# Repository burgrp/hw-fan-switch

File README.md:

# hw-fan-switch

A small, wirelessly-controlled 12 V DC fan switch. It drives a fan with a
variable PWM duty cycle and is controlled over a BLE long-range radio link,
making it part of the [Bleriot](https://github.com/burgrp/bleriot) node network.

The board is built around a **Puya PY32F003** Cortex-M0+ microcontroller with a
**PAN211x** radio, and the firmware is written in Go and compiled with
[TinyGo](https://tinygo.org/).

## Features

- Variable-speed fan control via hardware PWM (TIM14_CH1 on `PB1`).
- 50 kHz PWM carrier, above the audible range to avoid switching noise.
- Configurable low-speed handling:
  - **Low-duty threshold** — below this duty the fan is treated as stopped and
    the output is forced to 0.
  - **Low-duty kickstart** — a brief higher-duty pulse to overcome fan stiction
    when starting at low speed.
- Wireless control and telemetry over the PAN211x BLE long-range link.
- Yellow status LED is steadily on while the hub is online and flashes briefly
  once per second while offline.
- Device identity, radio settings, and configuration are owned by the site
  inventory and baked into each firmware image at build time.

## Repository layout

| Path | Description |
| --- | --- |
| `board/` | KiCad hardware design (schematic, PCB, BOM, production files). |
| `fw/` | Importable TinyGo firmware and board-owned build profile. |
| `fw/spec/` | Device specification: registers and runtime `Config`. |
| `fw/cmd/dev/` | Optional local development inventory. |
| `sub/hw-kicad/` | Shared KiCad symbol/footprint library (git submodule). |

## Hardware

| Function | Pin |
| --- | --- |
| Yellow status LED | `PB0` |
| Fan PWM output (TIM14_CH1, AF0) | `PB1` |
| Radio SPI clock | `PA2` |
| Radio SPI data | `PA1` |
| Radio SPI chip select | `PA4` |

The status LED is active high. A successfully decoded hub packet keeps the node
online for five seconds. While online the LED remains on; after the timeout it
follows BleRiot's 200 ms on, 800 ms off heartbeat until another packet arrives.

The KiCad project lives in `board/`, with fabrication outputs (Gerbers, BOM,
positions) under `board/production/`.

## Firmware

The firmware is the importable `fanswitch` package. Its TinyGo implementation
exports `Run`, while `fw/spec` exposes `Config`, the register table, chip, and a
typed build/flash profile. BleRiot generates a private external `package main`
inside the deployment module and calls `Run` with that instance's baked identity
and configuration. Nothing is generated in this repository for a deployment
build.

### Prerequisites

- [TinyGo](https://tinygo.org/getting-started/install/)
- [pyOCD](https://pyocd.io/) for flashing and RTT logging
- `arm-none-eabi-objdump` (optional, for disassembly)

Clone with submodules:

```sh
git clone --recurse-submodules https://github.com/burgrp/hw-fan-switch.git
```

### Build and flash

Build deployment firmware from the authoritative site inventory. For the AGC
checkout and its `basement.fan` instance:

```sh
cd /home/paul/git/agc/bleriot

# Inspect the generated entry point without writing it
go run . node gen --name basement.fan

# One-time: install the target CMSIS pack
go run . node install-pack --name basement.fan

# Generate the private entry point and build image.elf
go run . node build --name basement.fan

# Generate, build, flash, and open RTT
go run . node build --name basement.fan --flash --rtt

# Open RTT without flashing
go run . node rtt --name basement.fan
```

The `bleriot node` commands resolve the selected inventory instance. `node
build` generates its identity and `Config` under that deployment's private
`.bleriot` directory, then builds this module using the profile carried by
`spec.Type`. The deployment pins the firmware version in `go.mod`; it does not
carry fan-specific build flags. This repository's Makefile contains optional
aliases for `fw/cmd/dev`.

## Configuration

The inventory `Config` (see `fw/spec/spec.go`) controls runtime behaviour:

| Field | Meaning |
| --- | --- |
| `DefaultDuty` | Fan duty cycle (0–100) applied at startup. |
| `LowDutyThreshold` | Duty below which the fan is forced to 0. `0` disables the threshold. |
| `LowDutyKickstart` | Duty briefly applied to spin up the fan from low speed. `0` disables the kickstart. |

## Control interface

The device exposes a single register over the Bleriot network:

| Register | Tag | Type | Unit | Description |
| --- | --- | --- | --- | --- |
| `duty` | 1 | int | % | PWM duty cycle, 0–100. |

Writing `duty` updates the fan speed; the hub's next scheduled GET observes the
new value. A NULL write stops the fan. Reading returns the current duty.

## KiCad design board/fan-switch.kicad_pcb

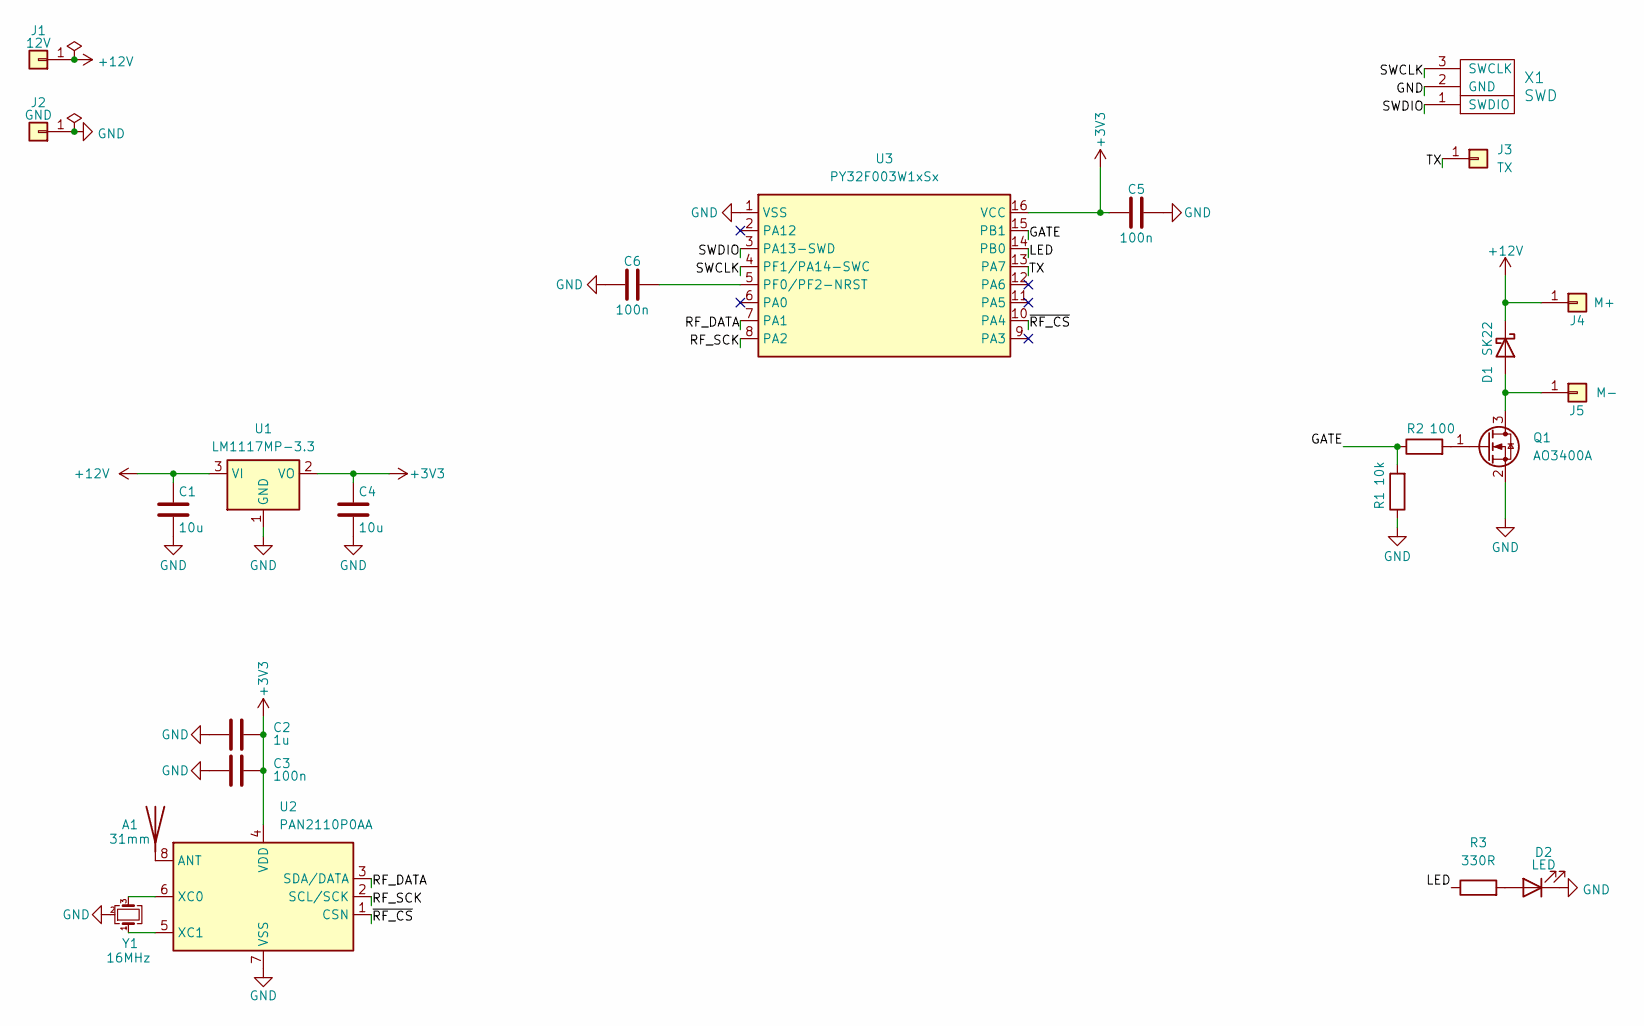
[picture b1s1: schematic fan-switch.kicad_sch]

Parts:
A1: 31mm; Wire antena 2.4GHz
C1, C4: 10u; C_0805_2012Metric
C2: 1u; C_0805_2012Metric
C3, C5, C6: 100n; C_0805_2012Metric
D1: SK22; D_SMB_Handsoldering
D2: LED; LED_0805_2012Metric_Pad1.15x1.40mm_HandSolder
J1: 12V; SolderWire-1sqmm_1x01_D1.4mm_OD3.9mm
J2: GND; SolderWire-1sqmm_1x01_D1.4mm_OD3.9mm
J3: TX; PinHeader_1x01_P2.54mm_Vertical
J4: M+; SolderWire-1sqmm_1x01_D1.4mm_OD3.9mm
J5: M-; SolderWire-1sqmm_1x01_D1.4mm_OD3.9mm
Q1: AO3400A; SOT-23
R1: 10k; R_0805_2012Metric_Pad1.20x1.40mm_HandSolder
R2: 100; R_0805_2012Metric_Pad1.20x1.40mm_HandSolder
R3: 330R; R_0805_2012Metric_Pad1.20x1.40mm_HandSolder
U1: LM1117MP-3.3; SOT-223-3_TabPin2
U2: PAN2110P0AA; SOIC-8_3.9x4.9mm_P1.27mm
U3: PY32F003W1xSx; SOIC-16_3.9x9.9mm_P1.27mm
X1: SWD
Y1: 16MHz; Crystal_SMD_3225-4Pin_3.2x2.5mm

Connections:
+3V3: C2.1, C3.1, C4.1, C5.1, U1.2 (VO), U2.4 (VDD), U3.16 (VCC)
+12V: C1.1, D1.1 (K), J1.1, J4.1, U1.3 (VI)
/GATE: R1.2, R2.1, U3.15 (PB1)
/LED: R3.1, U3.14 (PB0)
/RF_DATA: U2.3 (SDA/DATA), U3.7 (PA1)
/RF_SCK: U2.2 (SCL/SCK), U3.8 (PA2)
/SWCLK: U3.4 (PF1/PA14-SWC), X1.3 (SWCLK)
/SWDIO: U3.3 (PA13-SWD), X1.1 (SWDIO)
/TX: J3.1, U3.13 (PA7)
/~RF_CS: U2.1 (CSN), U3.10 (PA4)
GND: C1.2, C2.2, C3.2, C4.2, C5.2, C6.2, D2.1 (K), J2.1, Q1.2 (S), R1.1, U1.1 (GND), U2.7 (VSS), U3.1 (VSS), X1.2 (GND), Y1.2 (G), Y1.4 (G)
unnamed: A1.1 (A), U2.8 (ANT)
unnamed: D1.2 (A), J5.1, Q1.3 (D)
unnamed: D2.2 (A), R3.2
unnamed: Q1.1 (G), R2.2
unnamed: U2.6 (XC0), Y1.3
unnamed: U2.5 (XC1), Y1.1
unnamed: C6.1, U3.5 (PF0/PF2-NRST)

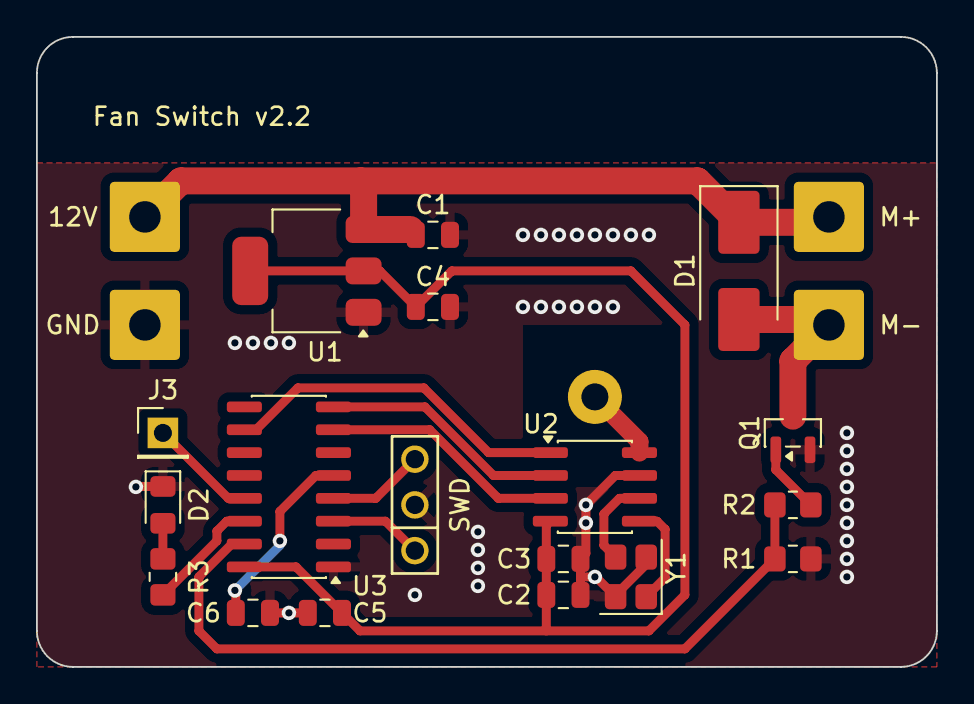
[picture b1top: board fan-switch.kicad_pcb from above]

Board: 2 copper layers, 50.0 x 35.0 mm, 23 parts (0 on the bottom side), 18 nets.

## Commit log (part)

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2026-06-23 Refactor firmware structure and update configuration files; remove deprecated files and add new settings for TinyGo environment
2026-06-25 Refactor fan control firmware: update configurations, modify GPIO handling, and streamline dependencies
2026-06-26 Refactor fan control and update schematic
    - Updated fan PWM configuration in main.go to use TIM14 on PB1 with a frequency of 50 kHz.
    - Added setupFanPWM and setFanDuty methods to manage fan speed via PWM.
    - Adjusted pin assignments for SPI communication.
    - Modified the schematic to reflect new pin locations and updated component positions.
    - Changed Makefile to include new commands for project management.
    - Updated test-hub.go with new UID and Key values for the fan device.
2026-06-26 Update fan control logic: enable LED on duty cycle change and remove unused ledLoop function
2026-06-26 Refactor fan control: update duty cycle thresholds and add StartNode function for PAN211x radio
2026-06-26 Enhance memory reporting: update RAM statistics logging and remove unused memstat function
2026-06-26 Refactor dependency management: update go.mod and go.sum for tinygo-drivers and remove unused pan211x package
2026-06-26 Add low duty cycle configuration: introduce LowDutyThreshold and LowDutyKickstart in Config struct and update fan control logic
2026-06-26 Update hub command: add diagnostics flag for RF diagnostics
2026-06-26 Fix module path in go.mod and update import path in main.go
2026-06-26 Update module path in go.mod and main.go to reflect repository name change
2026-06-26 Add metadata for duty cycle unit in device type specification
2026-06-26 Remove obsolete firmware files and configuration templates
2026-06-26 Update README.md with detailed project description, features, and usage instructions
2026-06-26 Refactor code structure for improved readability and maintainability
